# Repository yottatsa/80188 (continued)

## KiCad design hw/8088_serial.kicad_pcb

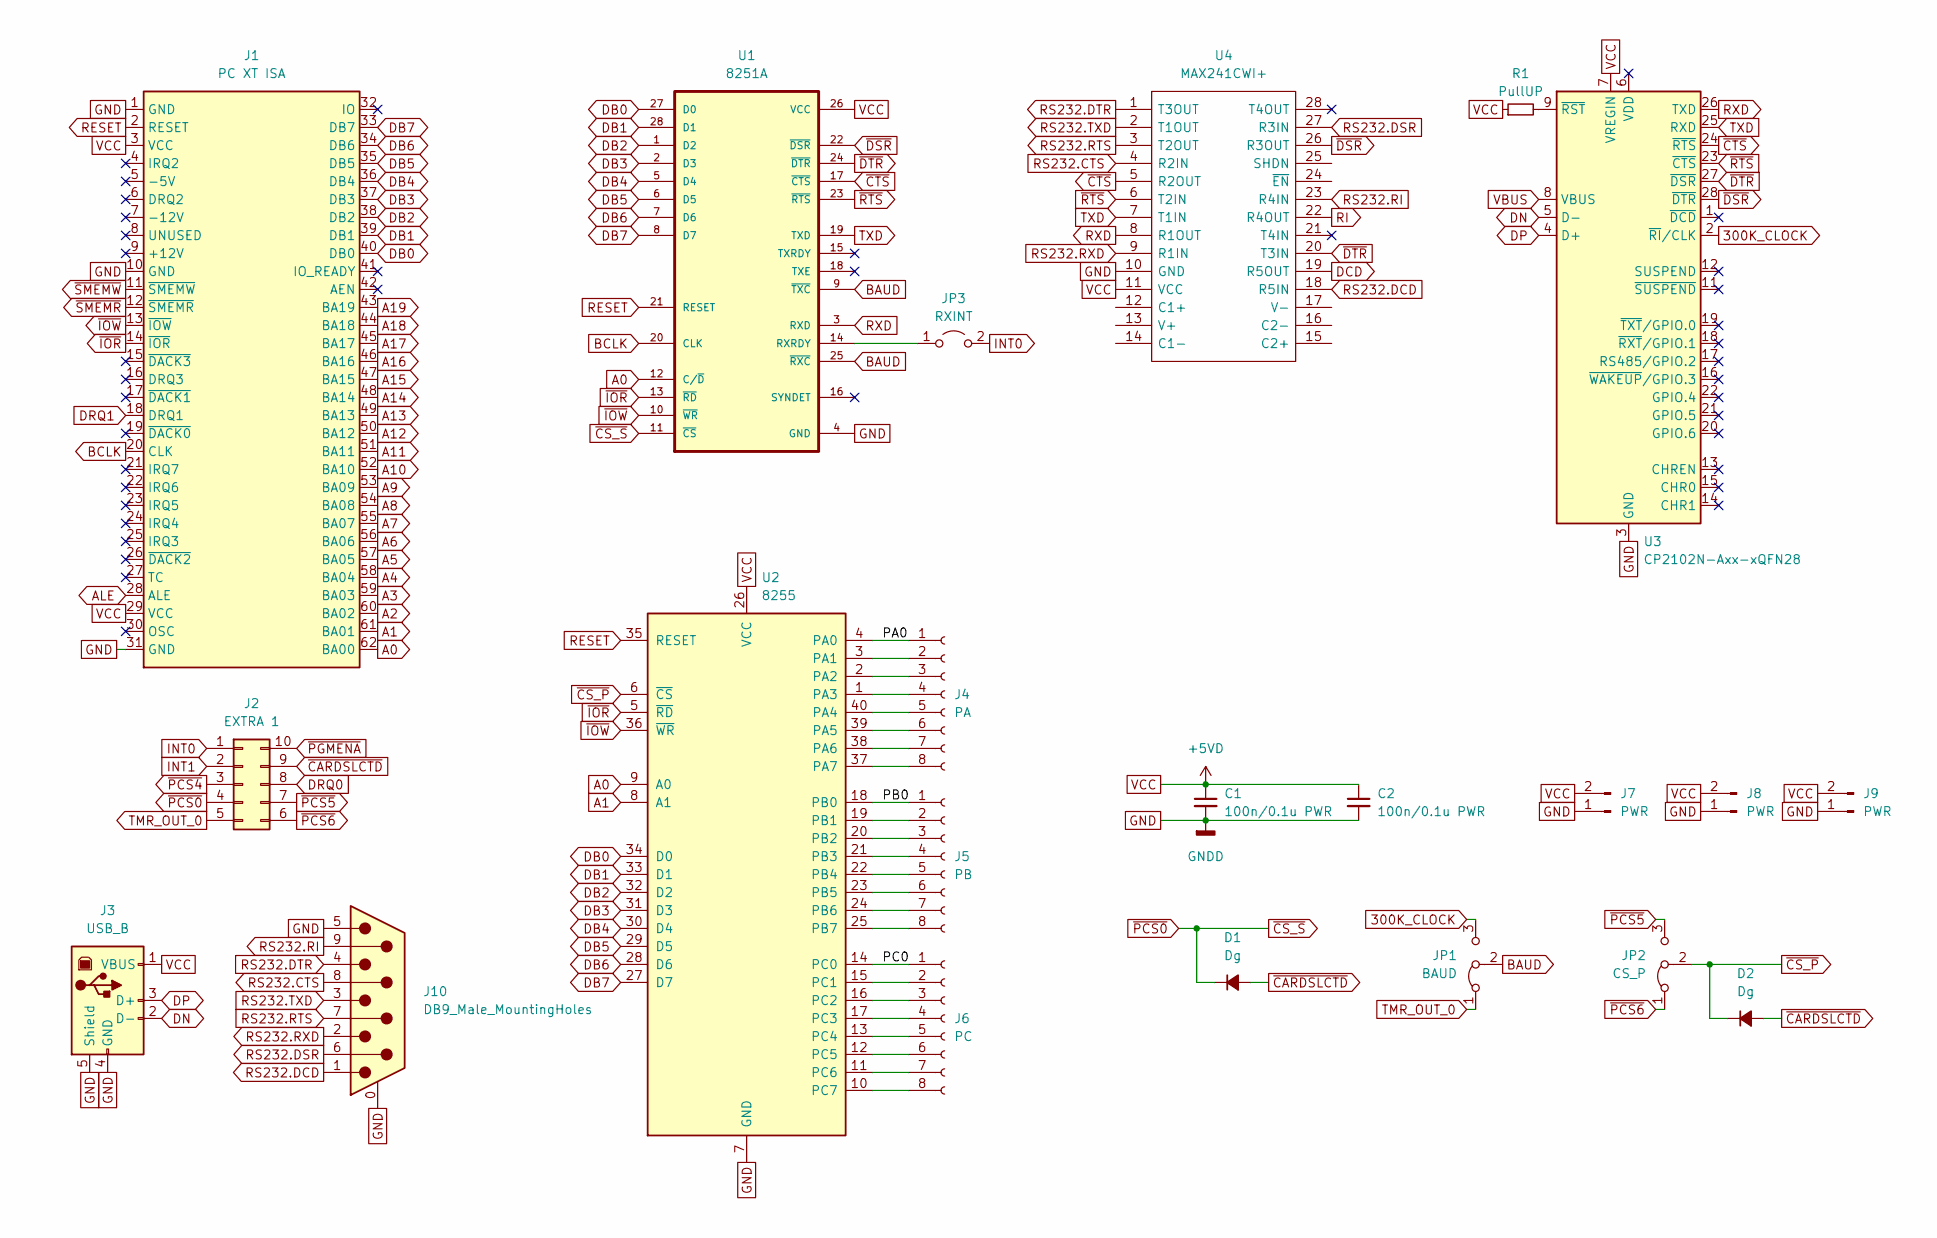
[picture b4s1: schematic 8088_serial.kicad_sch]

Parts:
C1, C2: 100n/0.1u PWR; C_1206_3216Metric_Pad1.33x1.80mm_HandSolder; Mouser Part Number 80-C1206X104G4HACTU
D1, D2: Dg; D_SOD-323_HandSoldering
J1: PC XT ISA; ISA-X
J2: EXTRA 1; 80188 EXTRA
J3: USB_B; USB_B_OST_USB-B1HSxx_Horizontal
J4: PA; PinHeader_1x08_P2.54mm_Vertical
J5: PB; PinHeader_1x08_P2.54mm_Vertical
J6: PC; PinHeader_1x08_P2.54mm_Vertical
J7, J8, J9: PWR; PinHeader_1x02_P2.54mm_Vertical
J10: DB9_Male_MountingHoles; DSUB-9_Male_Horizontal_P2.77x2.84mm_EdgePinOffset7.70mm_Hou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
JP1: BAUD; SolderJumper-3_P1.3mm_Open_RoundedPad1.0x1.5mm
JP2: CS_P; SolderJumper-3_P1.3mm_Open_RoundedPad1.0x1.5mm
JP3: RXINT; SolderJumper-2_P1.3mm_Open_RoundedPad1.0x1.5mm
R1: PullUP; R_1206_3216Metric_Pad1.30x1.75mm_HandSolder; Mouser Part Number 71-RCC120620K0FKEA
U1: 8251A; DIP-28_W15.24mm_Socket
U2: 8255; DIP-40_W15.24mm_Socket
U3: CP2102N-Axx-xQFN28; QFN-28-1EP_5x5mm_P0.5mm_EP3.35x3.35mm
U4: MAX241CWI+; SOIC127P1032X265-28N; Manufacturer_Part_Number MAX241CWI+

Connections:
300K_CLOCK: JP1.3 (B), U3.2 (~RI/CLK)
/PA0: J4.1, U2.4 (PA0)
/PB0: J5.1, U2.18 (PB0)
/PC0: J6.1, U2.14 (PC0)
A0: J1.62 (BA00), U1.12 (C/~D), U2.9 (A0)
A1: J1.61 (BA01), U2.8 (A1)
A2: J1.60 (BA02)
A3: J1.59 (BA03)
A4: J1.58 (BA04)
A5: J1.57 (BA05)
A6: J1.56 (BA06)
A7: J1.55 (BA07)
A8: J1.54 (BA08)
A9: J1.53 (BA09)
A10: J1.52 (BA10)
A11: J1.51 (BA11)
A12: J1.50 (BA12)
A13: J1.49 (BA13)
A14: J1.48 (BA14)
A15: J1.47 (BA15)
A16: J1.46 (BA16)
A17: J1.45 (BA17)
A18: J1.44 (BA18)
A19: J1.43 (BA19)
ALE: J1.28 (ALE)
BAUD: JP1.2 (C), U1.9 (~TXC), U1.25 (~RXC)
BCLK: J1.20 (CLK), U1.20 (CLK)
DB0: J1.40 (DB0), U1.27 (D0), U2.34 (D0)
DB1: J1.39 (DB1), U1.28 (D1), U2.33 (D1)
DB2: J1.38 (DB2), U1.1 (D2), U2.32 (D2)
DB3: J1.37 (DB3), U1.2 (D3), U2.31 (D3)
DB4: J1.36 (DB4), U1.5 (D4), U2.30 (D4)
DB5: J1.35 (DB5), U1.6 (D5), U2.29 (D5)
DB6: J1.34 (DB6), U1.7 (D6), U2.28 (D6)
DB7: J1.33 (DB7), U1.8 (D7), U2.27 (D7)
DN: J3.2 (D-), U3.5 (D-)
DP: J3.3 (D+), U3.4 (D+)
DRQ0: J2.8
DRQ1: J1.18 (DRQ1)
GND: C1.2, C2.2, J1.1 (GND), J1.10 (GND), J1.31 (GND), J3.4 (GND), J3.5 (Shield), J7.1, J8.1, J9.1, J10.0 (PAD), J10.5, U1.4 (GND), U2.7 (GND), U3.3 (GND), U3.29 (GND), U4.10 (GND)
INT0: J2.1, JP3.2 (B)
INT1: J2.2
unnamed: J4.2, U2.3 (PA1)
unnamed: J4.3, U2.2 (PA2)
unnamed: J4.4, U2.1 (PA3)
unnamed: J4.5, U2.40 (PA4)
unnamed: J4.6, U2.39 (PA5)
unnamed: J4.7, U2.38 (PA6)
unnamed: J4.8, U2.37 (PA7)
unnamed: J5.2, U2.19 (PB1)
unnamed: J5.3, U2.20 (PB2)
unnamed: J5.4, U2.21 (PB3)
unnamed: J5.5, U2.22 (PB4)
unnamed: J5.6, U2.23 (PB5)
unnamed: J5.7, U2.24 (PB6)
unnamed: J5.8, U2.25 (PB7)
unnamed: J6.2, U2.15 (PC1)
unnamed: J6.3, U2.16 (PC2)
unnamed: J6.4, U2.17 (PC3)
unnamed: J6.5, U2.13 (PC4)
unnamed: J6.6, U2.12 (PC5)
unnamed: J6.7, U2.11 (PC6)
unnamed: J6.8, U2.10 (PC7)
unnamed: JP3.1 (A), U1.14 (RXRDY)
unnamed: R1.2, U3.9 (~RST)
RESET: J1.2 (RESET), U1.21 (RESET), U2.35 (RESET)
RS232.CTS: J10.8, U4.4 (R2IN)
RS232.DCD: J10.1, U4.18 (R5IN)
RS232.DSR: J10.6, U4.27 (R3IN)
RS232.DTR: J10.4, U4.1 (T3OUT)
RS232.RI: J10.9, U4.23 (R4IN)
RS232.RTS: J10.7, U4.3 (T2OUT)
RS232.RXD: J10.2, U4.9 (R1IN)
RS232.TXD: J10.3, U4.2 (T1OUT)
RXD: U1.3 (RXD), U3.26 (TXD), U4.8 (R1OUT)
TMR_OUT_0: J2.5, JP1.1 (A)
TXD: U1.19 (TXD), U3.25 (RXD), U4.7 (T1IN)
VBUS: U3.8 (VBUS)
VCC: C1.1, C2.1, J1.3 (VCC), J1.29 (VCC), J3.1 (VBUS), J7.2, J8.2, J9.2, R1.1, U1.26 (VCC), U2.26 (VCC), U3.7 (VREGIN), U4.11 (VCC)
~CS_P: D2.1 (K), JP2.2 (C), U2.6 (~CS)
~CS_S: D1.1 (K), J2.4, U1.11 (~CS)
~CTS: U1.17 (~CTS), U3.24 (~RTS), U4.5 (R2OUT)
~DSR: U1.22 (~DSR), U3.28 (~DTR), U4.26 (R3OUT)
~DTR: U1.24 (~DTR), U3.27 (~DSR), U4.20 (T3IN)
~IOR: J1.14 (~IOR), U1.13 (~RD), U2.5 (~RD)
~IOW: J1.13 (~IOW), U1.10 (~WR), U2.36 (~WR)
~PACK: D1.2 (A), D2.2 (A), J2.9
~PCS4: J2.3
~PCS5: J2.7, JP2.3 (B)
~PCS6: J2.6, JP2.1 (A)
~PGMENA: J2.10
~RTS: U1.23 (~RTS), U3.23 (~CTS), U4.6 (T2IN)
~SMEMR: J1.12 (~SMEMR)
~SMEMW: J1.11 (~SMEMW)

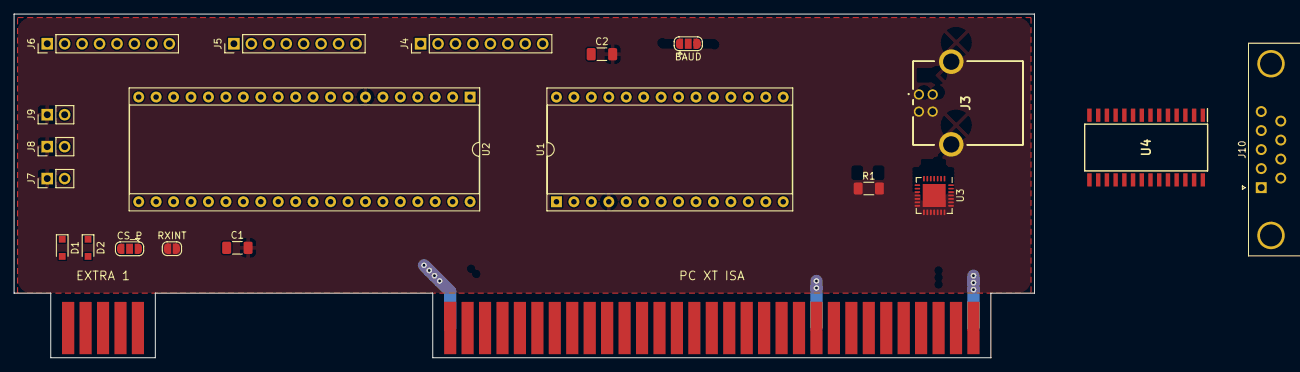
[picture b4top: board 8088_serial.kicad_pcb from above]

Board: 2 copper layers, 148.6 x 50.0 mm, 22 parts (0 on the bottom side), 67 nets.

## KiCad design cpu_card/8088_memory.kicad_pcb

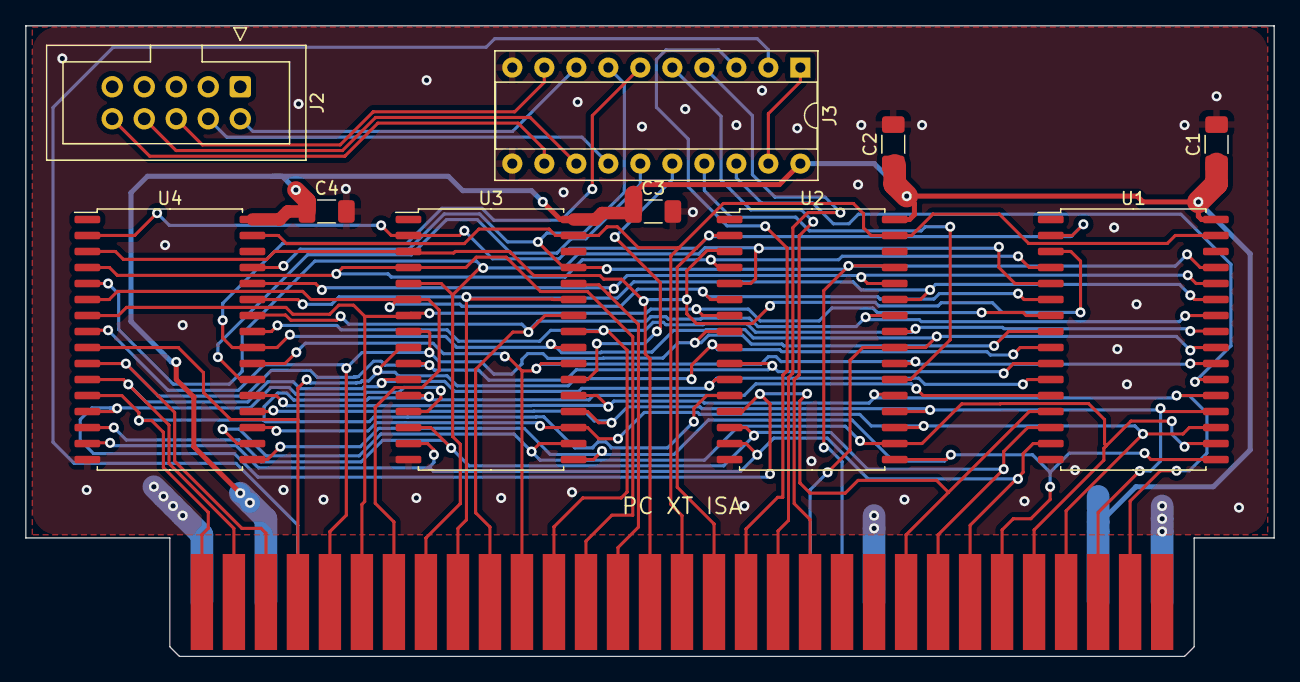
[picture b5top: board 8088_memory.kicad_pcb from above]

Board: 2 copper layers, 99.1 x 50.0 mm, 11 parts (0 on the bottom side), 43 nets.

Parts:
C1, C2, C3, C4: 100n/0.1u PWR; C_1206_3216Metric_Pad1.33x1.80mm_HandSolder
J1: PC XT ISA; ISA-X
J2: EXTRA 1; IDC-Header_2x05_P2.54mm_Vertical
J3: GAL16V8; DIP-20_W7.62mm_Socket
U1, U2, U3, U4: SRAM; SSOP-32_11.305x20.495mm_P1.27mm

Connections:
A0: J1.62 (BA00), U1.12 (A0), U2.12 (A0), U3.12 (A0), U4.12 (A0)
A1: J1.61 (BA01), U1.11 (A1), U2.11 (A1), U3.11 (A1), U4.11 (A1)
A2: J1.60 (BA02), U1.10 (A2), U2.10 (A2), U3.10 (A2), U4.10 (A2)
A3: J1.59 (BA03), U1.9 (A3), U2.9 (A3), U3.9 (A3), U4.9 (A3)
A4: J1.58 (BA04), U1.8 (A4), U2.8 (A4), U3.8 (A4), U4.8 (A4)
A5: J1.57 (BA05), U1.7 (A5), U2.7 (A5), U3.7 (A5), U4.7 (A5)
A6: J1.56 (BA06), U1.6 (A6), U2.6 (A6), U3.6 (A6), U4.6 (A6)
A7: J1.55 (BA07), U1.5 (A7), U2.5 (A7), U3.5 (A7), U4.5 (A7)
A8: J1.54 (BA08), U1.27 (A8), U2.27 (A8), U3.27 (A8), U4.27 (A8)
A9: J1.53 (BA09), U1.26 (A9), U2.26 (A9), U3.26 (A9), U4.26 (A9)
A10: J1.52 (BA10), U1.23 (A10), U2.23 (A10), U3.23 (A10), U4.23 (A10)
A11: J1.51 (BA11), U1.25 (A11), U2.25 (A11), U3.25 (A11), U4.25 (A11)
A12: J1.50 (BA12), U1.4 (A12), U2.4 (A12), U3.4 (A12), U4.4 (A12)
A13: J1.49 (BA13), U1.28 (A13), U2.28 (A13), U3.28 (A13), U4.28 (A13)
A14: J1.48 (BA14), U1.3 (A14), U2.3 (A14), U3.3 (A14), U4.3 (A14)
A15: J1.47 (BA15), U1.31 (A15), U2.31 (A15), U3.31 (A15), U4.31 (A15)
A16: J1.46 (BA16), U1.2 (A16), U2.2 (A16), U3.2 (A16), U4.2 (A16)
A17: J1.45 (BA17), J3.3 (I3)
A18: J1.44 (BA18), J3.4 (I4)
A19: J1.43 (BA19), J3.5 (I5)
ALE: J1.28 (ALE), J3.2 (I2)
DB0: J1.40 (DB0), U1.13 (Q0), U2.13 (Q0), U3.13 (Q0), U4.13 (Q0)
DB1: J1.39 (DB1), U1.14 (Q1), U2.14 (Q1), U3.14 (Q1), U4.14 (Q1)
DB2: J1.38 (DB2), U1.15 (Q2), U2.15 (Q2), U3.15 (Q2), U4.15 (Q2)
DB3: J1.37 (DB3), U1.17 (Q3), U2.17 (Q3), U3.17 (Q3), U4.17 (Q3)
DB4: J1.36 (DB4), U1.18 (Q4), U2.18 (Q4), U3.18 (Q4), U4.18 (Q4)
DB5: J1.35 (DB5), U1.19 (Q5), U2.19 (Q5), U3.19 (Q5), U4.19 (Q5)
DB6: J1.34 (DB6), U1.20 (Q6), U2.20 (Q6), U3.20 (Q6), U4.20 (Q6)
DB7: J1.33 (DB7), U1.21 (Q7), U2.21 (Q7), U3.21 (Q7), U4.21 (Q7)
GND: C1.2, C2.2, C3.2, C4.2, J1.1 (GND), J1.10 (GND), J1.31 (GND), J3.10 (GND), J3.11 (I10/~OE), U1.16 (GND), U2.16 (GND), U3.16 (GND), U4.16 (GND)
I8: J2.10, J3.8 (I8)
I9: J2.8, J3.9 (I9)
IO7: J2.7, J3.13 (IO7)
IO8: J2.6, J3.12 (IO8)
VCC: C1.1, C2.1, C3.1, C4.1, J1.3 (VCC), J1.29 (VCC), J3.20 (VCC), U1.32 (VCC), U2.32 (VCC), U3.32 (VCC), U4.32 (VCC)
~ALE: J3.1 (I1/CLK), J3.19 (IO1)
~CS1: J3.18 (IO2), U1.22 (~CS1)
~CS2: J3.17 (I03), U2.22 (~CS1)
~CS3: J3.16 (IO4), U3.22 (~CS1)
~CS4: J3.15 (IO5), U4.22 (~CS1)
~PACK: J2.9, J3.14 (IO6)
~SMEMR: J1.12 (~SMEMR), J3.6 (I6), U1.24 (~OE), U2.24 (~OE), U3.24 (~OE), U4.24 (~OE)
~SMEMW: J1.11 (~SMEMW), J3.7 (I7), U1.29 (~WE), U2.29 (~WE), U3.29 (~WE), U4.29 (~WE)

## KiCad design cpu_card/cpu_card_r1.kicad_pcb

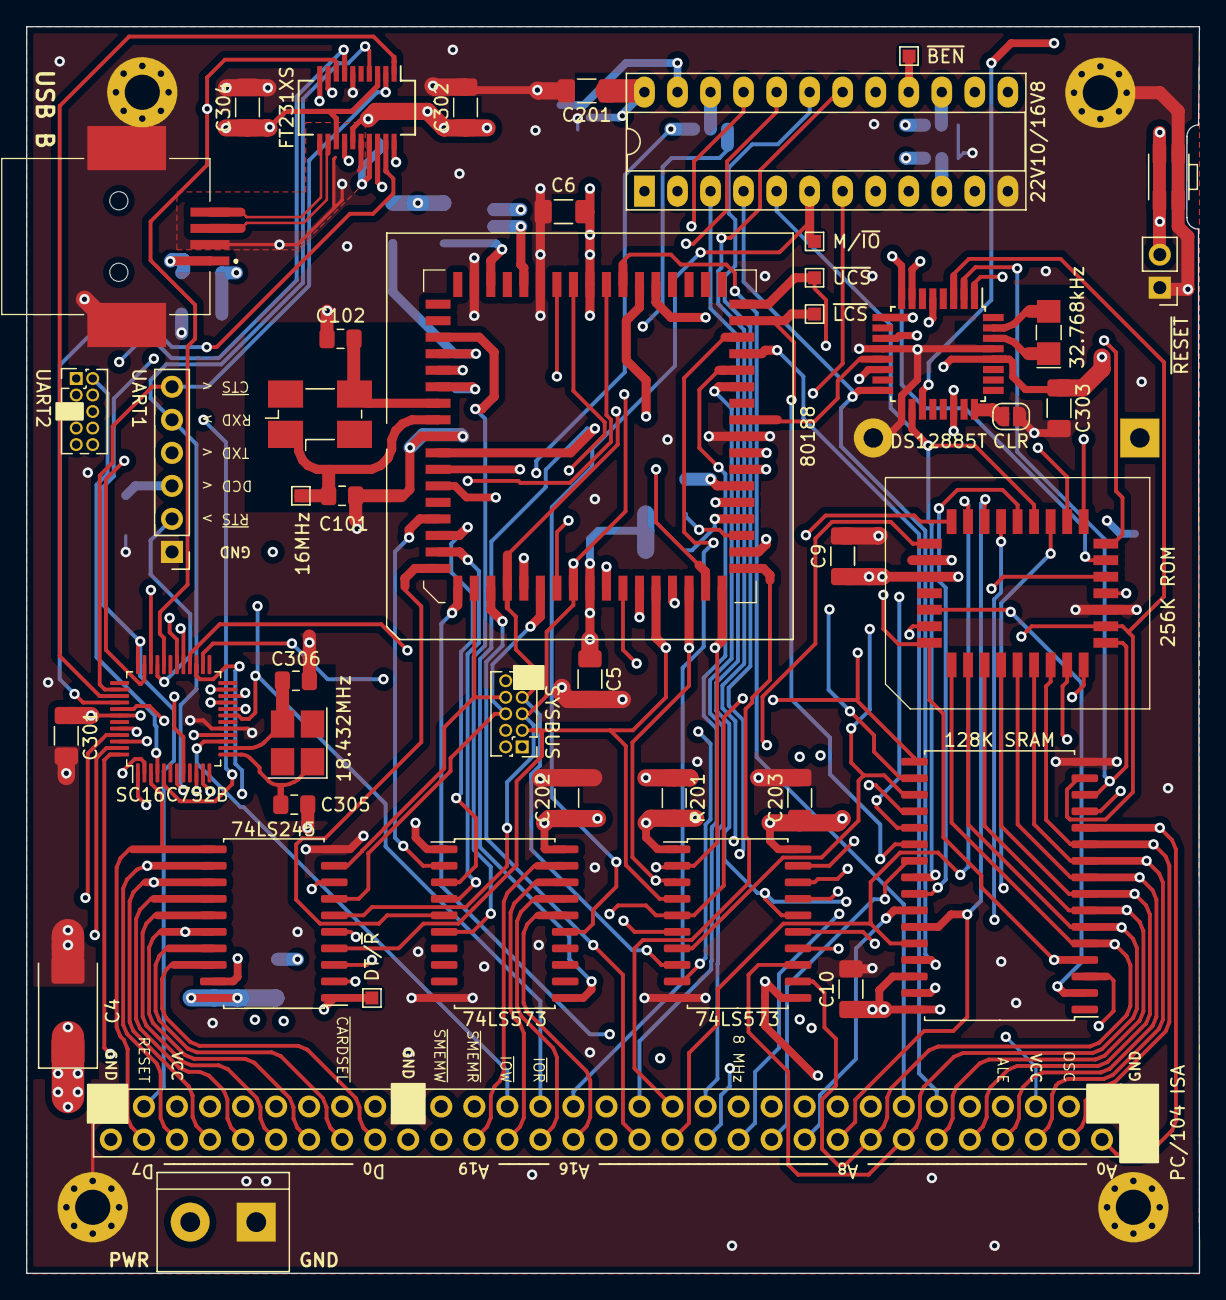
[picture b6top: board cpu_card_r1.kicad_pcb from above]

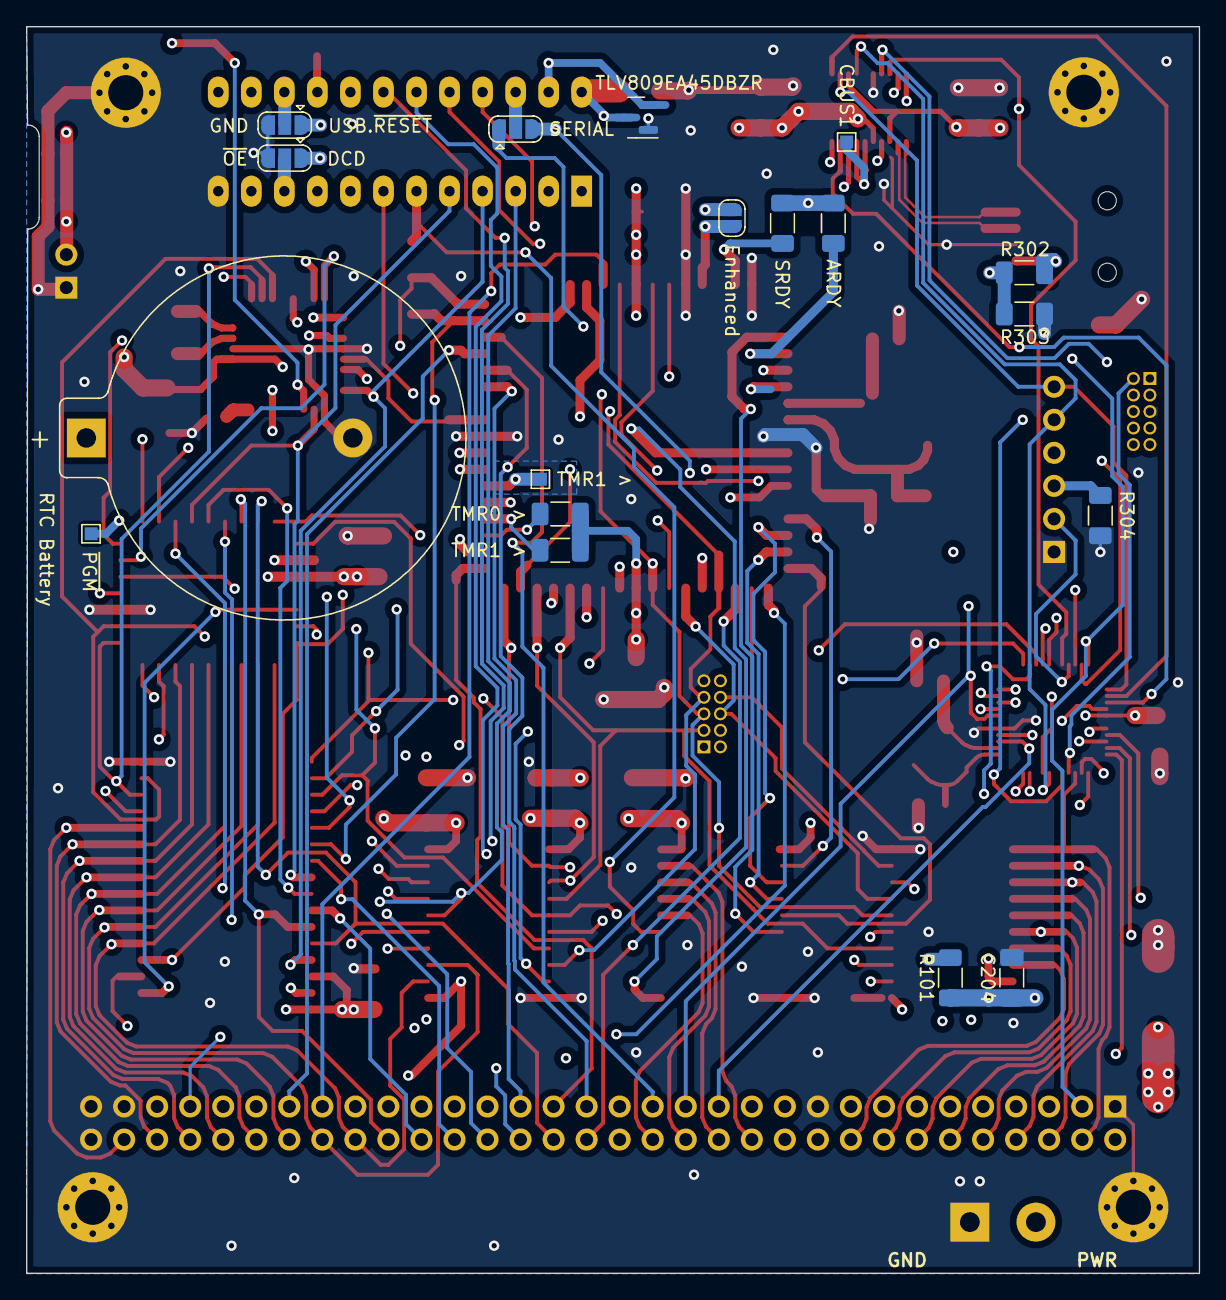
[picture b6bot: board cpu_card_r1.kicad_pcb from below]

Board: 4 copper layers, 90.2 x 95.8 mm, 67 parts (18 on the bottom side), 120 nets.

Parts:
BT301: RTC Battery; BatteryHolder_Keystone_106_1x20mm
C4: PPWR; CP_EIA-7343-31_Kemet-D
C5, C6, C9, C10, C201, C202, C203, C204, C301, C302, C303, C304: 100n/0.1u PWR; C_1206_3216Metric_Pad1.33x1.80mm_HandSolder
C101, C305: 22p XTAL; C_0805_2012Metric_Pad1.18x1.45mm_HandSolder
C102: 20p XTAL; C_0805_2012Metric_Pad1.18x1.45mm_HandSolder
C306: 33p XTAL; C_0805_2012Metric_Pad1.18x1.45mm_HandSolder
H1, H2, H3, H4: MountingHole_2.7mm_M2.5_Pad_Via
J1: 80188; PLCC-68_SMD-Socket
J2: PC/104 ISA; PinSocket_2x32_P2.54mm_Vertical
J4: 256K ROM; 69802132LF
J201: 22V10/16V8; DIP-24_W7.62mm_Socket_LongPads
J202: SYSBUS; PinHeader_2x05_P1.27mm_Vertical
J203: ~{RESET}; PinHeader_1x02_P2.54mm_Vertical
J301: UART1; PinHeader_1x06_P2.54mm_Vertical
J302: UART2; PinHeader_2x05_P1.27mm_Vertical
J303: USB B; AUSBBSMT
JP101: Enhanced; SolderJumper-2_P1.3mm_Open_RoundedPad1.0x1.5mm
JP201: ~{OE} DCD; SolderJumper-3_P1.3mm_Open_RoundedPad1.0x1.5mm
JP202: GND USB.~{RESET}; SolderJumper-3_P1.3mm_Open_RoundedPad1.0x1.5mm
JP203: SERIAL; SolderJumper-3_P1.3mm_Open_RoundedPad1.0x1.5mm
R1: TMR1 >; R_1206_3216Metric_Pad1.30x1.75mm_HandSolder
R2: ARDY; R_1206_3216Metric_Pad1.30x1.75mm_HandSolder
R3: SRDY; R_1206_3216Metric_Pad1.30x1.75mm_HandSolder
R4: TMR0 >; R_1206_3216Metric_Pad1.30x1.75mm_HandSolder
R101: PullUp; R_1206_3216Metric_Pad1.30x1.75mm_HandSolder
R201: Limit; R_1206_3216Metric_Pad1.30x1.75mm_HandSolder
R302: R4k7; R_1206_3216Metric_Pad1.30x1.75mm_HandSolder
R303: R10k; R_1206_3216Metric_Pad1.30x1.75mm_HandSolder
R304: PullDown; R_1206_3216Metric_Pad1.30x1.75mm_HandSolder
S1: PWR; TerminalBlock_bornier-2_P5.08mm
SW201: RESET; SW_SPST_EVQP7A
SW301: CLR; SolderJumper-2_P1.3mm_Open_RoundedPad1.0x1.5mm
TP101: XTAL; TestPoint_Pad_1.0x1.0mm
TP102: TMR1 >; TestPoint_Pad_1.0x1.0mm
TP103: ~{UCS}; TestPoint_Pad_1.0x1.0mm
TP104: ~{LCS}; TestPoint_Pad_1.0x1.0mm
TP105: ~{PGM}; TestPoint_Pad_1.0x1.0mm
TP201: M/~{IO}; TestPoint_Pad_1.0x1.0mm
TP202: DT/~{R}; TestPoint_Pad_1.0x1.0mm
TP203: ~{BEN}; TestPoint_Pad_1.0x1.0mm
TP302: CBUS1; TestPoint_Pad_1.0x1.0mm
U4: 128K SRAM; SSOP-32_11.305x20.495mm_P1.27mm
U201, U203: 74LS573; SOIC-20W_7.5x12.8mm_P1.27mm
U202: 74LS245; SOIC-20W_7.5x12.8mm_P1.27mm
U204: TLV809EA45DBZR; SOT-23
U301: SC16C752B; TQFP-48_7x7mm_P0.5mm
U302: FT231XS; SSOP-20_3.9x8.7mm_P0.635mm
U303: DS12885T; TQFP-32_7x7mm_P0.8mm
Y1: 16MHz; Crystal_SMD_0603-4Pin_6.0x3.5mm_HandSoldering
Y301: 18.432MHz; Crystal_SMD_3225-4Pin_3.2x2.5mm_HandSoldering
Y302: 32.768kHz; Crystal_SMD_EuroQuartz_EQ161-2Pin_3.2x1.5mm_HandSoldering

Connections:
16V8.GND: J201.15 (A0/O3), JP202.2 (C)
16V8.~OE: J201.10 (I8), JP201.2 (C)
/X1: C101.2, J1.59 (X1), TP101.1, Y1.1
/X2: C102.1, J1.58 (X2), Y1.3
A0: J2.62, J4.12 (A0), U4.12 (A0), U201.19 (Q0), U301.28 (A0)
A1: J2.60, J4.11 (A1), U4.11 (A1), U201.18 (Q1), U301.27 (A1)
A2: J2.58, J4.10 (A2), U4.10 (A2), U201.17 (Q2), U301.26 (A2)
A3: J2.56, J4.9 (A3), J201.3 (I1), U4.9 (A3), U201.16 (Q3)
A4: J2.54, J4.8 (A4), U4.8 (A4), U201.15 (Q4)
A5: J2.52, J4.7 (A5), U4.7 (A5), U201.14 (Q5)
A6: J2.50, J4.6 (A6), U4.6 (A6), U201.13 (Q6)
A7: J2.48, J4.5 (A7), U4.5 (A7), U201.12 (Q7)
A8: J1.16 (A8), J2.46, J4.27 (A8), U4.27 (A8)
A9: J1.14 (A9), J2.44, J4.26 (A9), U4.26 (A9)
A10: J1.12 (A10), J2.42, J4.23 (A10), U4.23 (A10)
A11: J1.10 (A11), J2.40, J4.25 (A11), U4.25 (A11)
A12: J1.7 (A12), J2.38, J4.4 (A12), U4.4 (A12)
A13: J1.5 (A13), J2.36, J4.28 (A13), U4.28 (A13)
A14: J1.3 (A14), J2.34, J4.29 (A14), U4.3 (A14)
A15: J1.1 (A15), J2.32, J4.3 (A15), U4.31 (A15)
A16: J2.30, J4.2 (A16), U4.2 (A16), U203.16 (Q3)
A17: J2.28, J4.30 (A17), U203.17 (Q2)
A18: J2.26, U203.18 (Q1)
A19: J2.24, U203.19 (Q0)
AD0: J1.17 (AD0), J4.13 (D0), J202.1, U4.13 (Q0), U201.2 (D0), U202.2 (A0), U303.1 (AD0)
AD1: J1.15 (AD1), J4.14 (D1), J202.2, U4.14 (Q1), U201.3 (D1), U202.3 (A1), U303.2 (AD1)
AD2: J1.13 (AD2), J4.15 (D2), J202.3, U4.15 (Q2), U201.4 (D2), U202.4 (A2), U303.3 (AD2)
AD3: J1.11 (AD3), J4.17 (D3), J202.4, U4.17 (Q3), U201.5 (D3), U202.5 (A3), U303.5 (AD3)
AD4: J1.8 (AD4), J4.18 (D4), J202.5, U4.18 (Q4), U201.6 (D4), U202.6 (A4), U303.7 (AD4)
AD5: J1.6 (AD5), J4.19 (D5), J202.6, U4.19 (Q5), U201.7 (D5), U202.7 (A5), U303.8 (AD5)
AD6: J1.4 (AD6), J4.20 (D6), J202.7, U4.20 (Q6), U201.8 (D6), U202.8 (A6), U303.9 (AD6)
AD7: J1.2 (AD7), J4.21 (D7), J202.8, U4.21 (Q7), U201.9 (D7), U202.9 (A7), U303.11 (AD7)
ALE: J1.61 (ALE/QS0), J2.55, U201.11 (Load), U203.11 (Load), U303.14 (AS)
BCLK: J1.56 (CLKOUT), J2.39
DB0: J2.18, U202.18 (B0), U301.44 (D0)
DB1: J2.16, U202.17 (B1), U301.45 (D1)
DB2: J2.14, U202.16 (B2), U301.46 (D2)
DB3: J2.12, U202.15 (B3), U301.47 (D3)
DB4: J2.10, U202.14 (B4), U301.48 (D4)
DB5: J2.8, U202.13 (B5), U301.1 (D5)
DB6: J2.6, U202.12 (B6), U301.2 (D6)
DB7: J2.4, U202.11 (B7), U301.3 (D7)
DCD: J301.3, JP201.1 (A), R304.2
DRQ0: J1.18 (DRQ0), J2.35
DRQ1: J1.19 (DRQ1), J2.11
DT/~R: J1.40 (DT/~R), TP202.1, U202.1 (A->B)
GND: BT301.2 (-), C4.2, C5.2, C6.2, C9.2, C10.2, C101.1, C102.2, C201.2, C202.2, C203.2, C204.2, C301.2, C302.2, C303.2, C304.2, C305.1, C306.2, H1.1, H2.1, H3.1, H4.1, J1.26 (VSS), J1.46 (NMI), J1.50 (HOLD), J1.60 (VSS), J2.1, J2.19, J2.61, J2.63, J2.64, J4.16 (GND), J201.12 (GND), J202.9, J203.1, J301.1, J302.5, J303.4 (GND), J303.5 (Shield), JP201.3 (B), JP202.3 (B), R303.2, R304.1, S1.1, SW201.2, SW301.1 (A), U4.16 (GND), U201.10 (GND), U202.10 (GND), U203.10 (GND), U204.1 (GND), U301.17 (GND), U302.6 (GND), U302.16 (GND), U303.12 (GND), U303.17 (GND), U303.29 (MOT)
INT0: J1.45 (INT0), U301.30 (INTA)
INT1: J1.44 (INT1/~SELECT), J2.7
INT2: J1.42 (INT2/~INTA0), U301.29 (INTB)
INT3: J1.41 (INT3/~INTA1/IRQ), J2.49
M/~IO: J201.6 (I4), TP201.1, U203.15 (Q4)
unnamed: C305.2, U301.13 (XTAL1), Y301.1
unnamed: C306.1, U301.14 (XTAL2), Y301.3
unnamed: J1.20 (TMR_IN_0), R4.2
unnamed: J1.21 (TMR_IN_1), R1.2
unnamed: J1.23 (TMR_OUT_1), TP102.1
unnamed: J1.47 (~TEST), JP101.2 (B)
unnamed: J1.49 (SRDY), R3.2
unnamed: J1.55 (ARDY), R2.2
unnamed: J4.31 (~PGM), TP105.1
unnamed: J201.22 (O1/A0), JP203.2 (C)
unnamed: SW301.2 (B), U303.24 (~RCLR)
unnamed: TP302.1, U302.17 (CBUS1)
unnamed: U303.30 (X1), Y302.1
unnamed: U303.31 (X2), Y302.2
RESET: J2.3, J201.17 (A2/O1), U301.36 (RESET)
RESOUT: J1.57 (RESET), J201.2 (I0), JP101.1 (A)
TMR_OUT_0: J1.22 (TMR_OUT_0), J2.59
UART1.IN: J301.4, U301.5 (RXA), U302.20 (TXD)
UART1.OUT: J301.5, U301.7 (TXA), U302.4 (RXD)
UART1.~CTS: J301.6, U301.38 (~CTSA), U302.2 (~RTS)
UART1.~DSR: U301.39 (~DSRA), U302.1 (~DTR)
UART1.~DTR: U301.34 (~DTRA), U302.7 (~DSR)
UART1.~RI: U301.41 (~RIA), U302.10 (CBUS2)
UART1.~RTS: J301.2, U301.33 (~RTSA), U302.9 (~CTS)
UART2.RX: J302.2, U301.4 (RXB)
UART2.TX: J302.3, U301.8 (TXB)
UART2.~CD: J302.1, U301.16 (~CDB)
UART2.~CTS: J302.8, U301.23 (~CTSB)
UART2.~DSR: J302.6, U301.20 (~DSRB)
UART2.~DTR: J302.4, U301.35 (~DTRB)
UART2.~RI: J302.9, U301.21 (~RIB)
UART2.~RTS: J302.7, U301.22 (~RTSB)
USB.D+: J303.3 (D+), U302.11 (USBDP)
USB.D-: J303.2 (D-), U302.12 (USBDM)
USB.VCC: C304.1, U302.3 (VCCIO), U302.13 (3V3OUT)
USB.~DCD: U301.32 (~OPA), U302.8 (~DCD)
USB.~PWREN: U301.40 (~CDA), U302.19 (CBUS3)
USB.~RESET: JP202.1 (A), U302.14 (~RESET)
VBAT: BT301.1 (+), U303.22 (VBAT)
VBUS: J303.1 (VBUS), R302.1
VBUS_SENSE: R302.2, R303.1, U302.18 (CBUS0)
VCC: C4.1, C5.1, C6.1, C9.1, C10.1, C201.1, C202.1, C203.1, C204.1, C301.1, C302.1, C303.1, J1.9 (VCC), J1.43 (VCC), J2.5, J2.57, J4.32 (VCC), J201.24 (VCC), R1.1, R2.1, R3.1, R4.1, R101.1, R201.1, S1.2, U4.30 (CS2), U4.32 (VCC), U201.20 (VCC), U202.20 (VCC), U203.20 (VCC), U204.3 (VCC), U301.42 (VCC), U302.15 (VCC), U303.28 (VCC)
XA16: J1.68 (A16/S3), U203.5 (D3)
XA17: J1.67 (A17/S4), U203.4 (D2)
XA18: J1.66 (A18/S5), U203.3 (D1)
XA19: J1.65 (A19/S6), U203.2 (D0)
~AL_OE: R201.2, U201.1 (OE), U203.1 (OE)
~BEN: J201.16 (A1/O2), TP203.1, U202.19 (CE)
~CARDSLCTD: J2.15, J201.8 (I6), R101.2
~CS_RTC: J1.27 (~PCS1), U303.13 (~CS)
~CS_S1: JP203.1 (A), U301.10 (~CSA)
~CS_S2: J201.14 (LR/O4), JP203.3 (B), U301.11 (~CSB)
~CS_S: J1.25 (~PCS0), J201.7 (I5)
~DEN: J1.39 (~DEN), J201.9 (I7)
~IOR: J2.27, J201.21 (O2/A1), U301.19 (~IOR)
~IOW: J2.25, J201.20 (O3/A2), U301.15 (~IOW)
~LCS: J1.33 (~LCS), TP104.1, U4.22 (~CS1)
~PCS3: J1.29 (~PCS3), J2.37
~PCS4: J1.30 (~PCS4), J2.33
~PCS5: J1.31 (~PCS5/A1), J2.51
~PCS6: J1.32 (~PCS6/A2), J2.29
~RD: J1.62 (~RD/~QSMD), J4.24 (~OE), J201.5 (I3), U4.24 (~OE), U303.18 (DS)
~RESET: J1.24 (~RES), J201.23 (O0/LR), J203.2, SW201.1, U204.2 (~RESET), U303.19 (~RESET)
~S2: J1.54 (~S2), U203.6 (D4)
~SMEMR: J2.23, J201.19 (O4/NC)
~SMEMW: J2.21, J201.18 (NC/O0)
~UCS: J1.34 (~UCS), J4.22 (~CE), TP103.1
~WR: J1.63 (~WR/QS1), J201.4 (I2), U4.29 (~WE), U303.16 (R/*W)

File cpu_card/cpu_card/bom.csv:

"Item","Qty","Reference(s)","Value","LibPart","Footprint","Datasheet","Allied_Number","Description","Height","Manufacturer_Name","Manufacturer_Part_Number","Mouser Part Number","Mouser Price/Stock","RS Part Number","RS Price/Stock"
"1","1","BT301","RTC Battery","Device:Battery_Cell","Battery:BatteryHolder_Keystone_106_1x20mm","https://www.mouser.co.uk/datasheet/2/215/06-745914.pdf","","","","","106","534-106","","",""
"2","1","C4","PPWR","Device:C_Polarized_Small","Capacitor_Tantalum_SMD:CP_EIA-7343-31_Kemet-D","~","","","","","","667-EEF-CS1D100R","","",""
"3","12","C5, C6, C9, C10, C201, C202, C203, C204, C301, C302, C303, C304","100n/0.1u PWR","Device:C_Small","Capacitor_SMD:C_1206_3216Metric_Pad1.33x1.80mm_HandSolder","~","","","","","","80-C1206X104G4HACTU","","",""
"4","2","C101, C305","22p XTAL","Device:C_Small","Capacitor_SMD:C_0805_2012Metric_Pad1.18x1.45mm_HandSolder","~","","","","","C0805C220J1GACTU","","","",""
"5","1","C102","20p XTAL","Device:C_Small","Capacitor_SMD:C_0805_2012Metric_Pad1.18x1.45mm_HandSolder","~","","","","","C0805C220J1GACTU","","","",""
"6","1","C306","33p XTAL","Device:C_Small","Capacitor_SMD:C_0805_2012Metric_Pad1.18x1.45mm_HandSolder","~","","","","","C0805C220J1GACTU","","","",""
"8","1","J1","80188","MCU_Intel:80188","80C188:PLCC-68_SMD-Socket","http://datasheets.chipdb.org/Intel/x86/8018x/datashts/27243002.PDF","","","","","8468-11B1-RK-TP","517-8468-11B1-RK-TP ","","",""
"9","1","J2","PC/104 ISA","Connector_Generic:Conn_02x32_Odd_Even","Connector_PinSocket_2.54mm:PinSocket_2x32_P2.54mm_Vertical","~","","","","","","","","",""
"10","1","J4","256K ROM","Memory_EPROM:27C020","69802-132LF:69802132LF","https://www.mouser.co.uk/datasheet/2/268/20005023B-709002.pdf","","","","","SST39SF020A-70-4C-NHE","804-39SF020A7CNHE ","","",""
"11","1","J201","22V10/16V8","Logic_Programmable:PAL24","Package_DIP:DIP-24_W7.62mm_Socket_LongPads","~","","","","","","","","",""
"12","1","J202","SYSBUS","Connector_Generic:Conn_02x05_Odd_Even","Connector_PinHeader_1.27mm:PinHeader_2x05_P1.27mm_Vertical","~","","","","","","","","",""
"13","1","J302","UART2","Connector_Generic:Conn_02x05_Odd_Even","Connector_PinSocket_1.27mm:PinSocket_2x05_P1.27mm_Vertical","~","","","","","","","","",""
"14","1","J303","USB B","Connector:USB_B","A-USB_B_SMT:AUSBBSMT","http://uk.rs-online.com/web/p/products/6741331P","R1074095","","","","A-USB B/SMT","","","6741331P","http://uk.rs-online.com/web/p/products/6741331P"
"15","1","R1","TMR1 >","Device:R_Small","Resistor_SMD:R_1206_3216Metric_Pad1.30x1.75mm_HandSolder","~","","1206 SMD 20 Kohms","","","","71-RCC120620K0FKEA","","",""
"16","1","R2","ARDY","Device:R_Small","Resistor_SMD:R_1206_3216Metric_Pad1.30x1.75mm_HandSolder","~","","1206 SMD 20 Kohms","","","","71-RCC120620K0FKEA","","",""
"17","1","R3","SRDY","Device:R_Small","Resistor_SMD:R_1206_3216Metric_Pad1.30x1.75mm_HandSolder","~","","1206 SMD 20 Kohms","","","","71-RCC120620K0FKEA","","",""
"18","1","R4","TMR0 >","Device:R_Small","Resistor_SMD:R_1206_3216Metric_Pad1.30x1.75mm_HandSolder","~","","1206 SMD 20 Kohms","","","","71-RCC120620K0FKEA","","",""
"19","1","R101","PullUp","Device:R_Small","Resistor_SMD:R_1206_3216Metric_Pad1.30x1.75mm_HandSolder","~","","1206 SMD 20 Kohms","","","","71-RCC120620K0FKEA","","",""
"20","1","R201","Limit","Device:R_Small","Resistor_SMD:R_1206_3216Metric_Pad1.30x1.75mm_HandSolder","~","","1206 SMD 20 Kohms","","","SFR18EZPJ000","755-SFR18EZPJ000","","",""
"21","1","R302","R4k7","Device:R","Resistor_SMD:R_1206_3216Metric_Pad1.30x1.75mm_HandSolder","~","","","","","CR1206-JW-472ELF ","652-CR1206-JW-472ELF","","",""
"22","1","R303","R10k","Device:R","Resistor_SMD:R_1206_3216Metric_Pad1.30x1.75mm_HandSolder","~","","","","","CR1206-JW-103ELF ","652-CR1206JW-103ELF","","",""
"23","1","R304","PullDown","Device:R_Small","Resistor_SMD:R_1206_3216Metric_Pad1.30x1.75mm_HandSolder","~","","1206 SMD 20 Kohms","","","","71-RCC120620K0FKEA","","",""
"24","1","S1","PWR","Connector:Screw_Terminal_01x02","TerminalBlock:TerminalBlock_bornier-2_P5.08mm","~","","","","","","","","",""
"25","1","SW201","RESET","Switch:SW_Push","Button_Switch_SMD:SW_SPST_EVQP7A","https://www.mouser.co.uk/datasheet/2/315/sw_lt_eng_3529s_sid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","","","","","EVQ-P7J01P","667-EVQP7J01P","","",""
"27","1","U4","128K SRAM","Memory_RAM:628128_DIP32_SSOP32","Package_SO:SSOP-32_11.305x20.495mm_P1.27mm","https://www.issi.com/WW/pdf/62-65C1024AL.pdf","","62C1024 128KB SRAM","","ISSI","IS62C1024AL-35QLI","","","",""
"28","2","U201, U203","74LS573","74xx:74LS573","Package_SO:SOIC-20W_7.5x12.8mm_P1.27mm","74xx/74hc573.pdf","","","","","74VHCT573AFT","","","171-3540",""
"29","1","U202","74LS245","74xx:74LS245","Package_SO:SOIC-20W_7.5x12.8mm_P1.27mm","https://www.mouser.co.uk/datasheet/2/308/1/MC74HCT245A_D-231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","","","","Texas Instruments","MC74HCT245ADWG","863-MC74HCT245ADWG","","",""
"30","1","U204","TLV809EA45DBZR","Power_Supervisor:TCM809","Package_TO_SOT_SMD:SOT-23","https://www.ti.com/lit/ds/symlink/tlv809e.pdf","","","","","","","","",""
"31","1","U301","SC16C752B","SC16C752BIB48_157:SC16C752BIB48,157","Package_QFP:TQFP-48_7x7mm_P0.5mm","http://www.nxp.com/docs/en/data-sheet/SC16C752B.pdf","","UART Interface IC 2CH. UART 64B FIFO","1.6","NXP","SC16C752BIB48,157","771-SC16C752BIB48","https://www.mouser.co.uk/ProductDetail/NXP-Semiconductors/SC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","",""
"32","1","U302","FT231XS","Interface_USB:FT231XS","Package_SO:SSOP-20_3.9x8.7mm_P0.635mm","https://www.ftdichip.com/Support/Documents/DataSheets/ICs/DS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","","","","","","","","",""
"33","1","U303","DS12885T","DS12885T:DS12885T","Package_QFP:TQFP-32_7x7mm_P0.8mm","","","","","","","","","",""
"34","1","Y1","16MHz","Device:Crystal_GND24_Small","Crystal:Crystal_SMD_0603-4Pin_6.0x3.5mm_HandSoldering","~","","RS PRO 16MHz Crystal ±30ppm SMT 4-Pin 6 x 3.5 x 1mm ","","","","","","",""
"35","1","Y301","18.432MHz","Device:Crystal_GND24_Small","Crystal:Crystal_SMD_3225-4Pin_3.2x2.5mm_HandSoldering","https://www.mouser.co.uk/datasheet/2/445/830105961709-2005258.pdf","","","","","830105961709","710-830105961709","","",""
"36","1","Y302","32.768kHz","Device:Crystal_Small","Crystal:Crystal_SMD_EuroQuartz_EQ161-2Pin_3.2x1.5mm_HandSoldering","https://www.mouser.co.uk/datasheet/2/122/ECX_34R-845158.pdf","","","","","ECS-.327-6-34R-TR","520-.327-6-34RT","","",""

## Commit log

2022-05-11 initial
2022-05-11 kicad project
2022-05-31 kinda working revision
2022-06-02 minimal viable board
    * PLD provides /IOW and TRG signals for reading all IO out
    * BIOS initialises the /UMCS and print debug
2022-06-02 readme
2022-06-05 minimal serial implementation
2022-06-06 timer as a baud rate generator
2022-06-06 stack and BIOS _getch
2022-06-06 echo, "memory test"
2022-06-19 debug in progress: reset error flag, serial timer to 4800
2022-06-22 cupl -> galasm
2022-06-22 board fixes
2022-06-29 debug part 1
    * pull-up for CARDSEL
    * memory test
    * test serial board on PCS3 and OSC/4 powered by timer1
2022-07-02 debug part 2
    * `_serial_putch` and `_serial_puts` macroses are reusable and working
    * checksum16
    * testing memory by bytes and by words
2022-07-25 new boad, rev 0.1.0
2022-07-27 gal for r0.1.0
2022-07-30 hw flow control for serial
    * GAL supports reading from serial
    * hw flow control initialised
2022-08-04 cleanup and docs
2022-08-06 Board revision R2 and isp_interface
    * `isp_interface` to re-program the on-board flash
    * fixes in R1
    - `/AL_OE` to `RESET`
    - capacitor on `/RESET`
2022-08-07 bios consoleio
2022-08-08 bios library and overall cleanup
2022-09-11 import minimal fake86-0.13.9.16
2022-09-11 minimal amd80c188.inc stub
2022-09-11 console output for emulator
2022-09-11 implemented basic DS12885 rtc/cmos
2022-09-12 v0.4: cleanup and emulation
    * keyboard input in emulator
    * better RTC assembly and macro
    * linting
    * some IBM PC XT endpoints
2022-09-12 fw: support for both binary and BCD RTC formats
2022-09-12 shortcuts
2022-09-17 blinkenlights initial integration
    Using https://justine.lol/blinkenlights/ to emulate BIOS ROM
    * imported https://github.com/jart/cosmopolitan
    * quick-and-dirty build using amalgamated libc
2022-09-18 cleanup
2022-09-18 cleanup: now builds with original amalgamated cosmo
2022-09-18 mvp, docs, licenses
2022-10-08 rtc macros, make cleanup
2022-10-08 _version should be null-terminated
2022-10-08 safer Nano-BIOS builtins
    Most macroses are using `BX` for argument passing, so it's preserved
    on stack now. It ate lots of space in the `.setup` segment, so it's
    moved to a segment between IBM XT entrypoint and the setupconsts.
    It's not covered by the checksum algorhytm now.
2022-10-11 examples directory and autoloader
2022-10-11 simple monitor
2022-10-11 comments
2022-10-11 Example binaries
    - "Hello World"
    - Brainfuck @ninakali
    - Monitor interface to invoke COM-files
    try
    make run COM=examples/bf
    <press %>
2022-10-15 bodge between SMEMW and EEPROM./WE
2022-11-25 interrupts; code reorg and comments
2022-11-27 interrupts
2022-11-27 monitor from 0xc0000 to 0xf0100
2023-04-10 docs
